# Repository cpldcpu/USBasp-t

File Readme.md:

## micro - USBasp ##

This is a work in progress. 

* Port of USBasp to ATtiny 85
* Design of optimized hardware

Why?

* It's fun.
* USBasp is a de-facto standard for small USB-AVR programmers. It's the only one to support TPI.
* Porting it to ATtiny85 allows for a smaller and cheaper circuit. Cheaper MCU, no Xtal, etc...

This software is based on Thomas Fischl's USBasp. See readme.txt for original comments.

### Status ####

Software:

* USBasp sucessfully compiles for the ATTiny85.
* micronucleus works as a bootloader.
* USB device is recognized as USBasp and communicates with AVRdude.
* Software tested on microUSB hardware. Both TPI and SPI seem to work.

Hardware:

* Revision 0.5 sent to OSH park for pcb manufacturing.
* Update v1.1 done, ready for manufacturing.
* Update 02/08/2013: All parts received, first device built.

### Flashing

* Flash micronucleus
* Set the fuses as in thuis Makefile: HFUSE=0x5d, LFUSE=0xe1, EFUSE=0xfe
* Flash the firmware with micronucleus

### Hardware ###

Circuit:  

v1.1 PCB front side:  

v1.1 PCB rear side:

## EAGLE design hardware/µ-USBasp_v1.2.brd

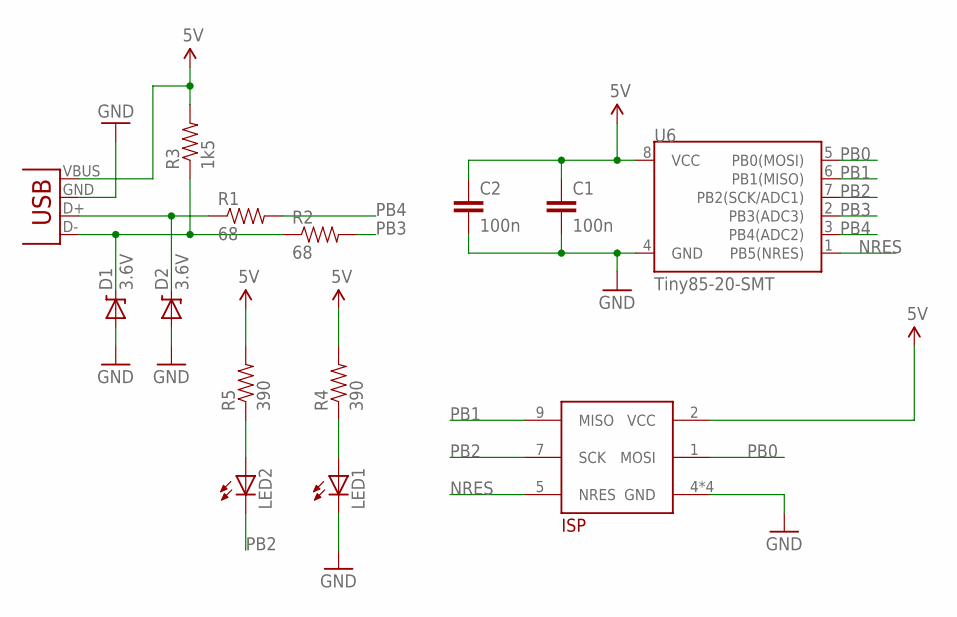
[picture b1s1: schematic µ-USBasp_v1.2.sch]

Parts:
C1, C2: 100n; 0805
D1, D2: 3.6V; SOD-323
JP2: USB-A-H
LED1, LED2: LEDCHIPLED_0805; CHIPLED_0805
R1, R2: 68; 0805
R3: 1k5; 0805
R4, R5: 390; 0805
U6: Tiny85-20-SMT; SO08-EIAJ
U$1: TB_ISPEDGE_2X5_LONG; ISP_EDGE2X5_LONG

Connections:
5V: C1.1, C2.1, JP2.VBUS (GND), R3.2, R4.2, R5.2, U6.8 (VCC), U$1.2 (VCC)
GND: C1.2, C2.2, D1.2 (A), D2.2 (A), JP2.GND (VBUS), LED1.C, U6.4 (GND), U$1.4 (GND), U$1.6 (GND), U$1.8 (GND), U$1.10 (GND)
unnamed: D1.1 (C), JP2.D- (D+), R2.1, R3.1
unnamed: D2.1 (C), JP2.D+ (D-), R1.1
unnamed: LED1.A, R4.1
unnamed: LED2.A, R5.1
NRES: U6.1 (PB5(NRES)), U$1.5 (NRES)
PB0: U6.5 (PB0(MOSI)), U$1.1 (MOSI)
PB1: U6.6 (PB1(MISO)), U$1.9 (MISO)
PB2: LED2.C, U6.7 (PB2(SCK/ADC1)), U$1.7 (SCK)
PB3: R2.2, U6.2 (PB3(ADC3))
PB4: R1.2, U6.3 (PB4(ADC2))

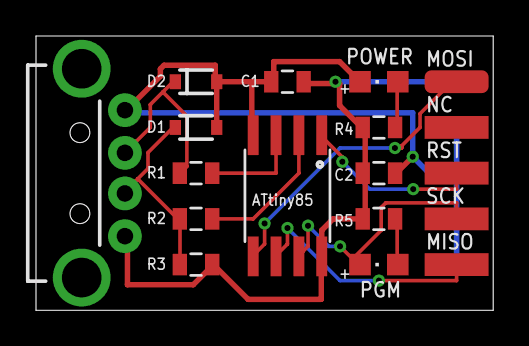
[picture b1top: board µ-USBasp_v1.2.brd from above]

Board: 2 copper layers, 25.4 x 15.2 mm, 15 parts (1 on the bottom side), 12 nets.

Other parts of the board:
U$2: OSHW-LOGO-M

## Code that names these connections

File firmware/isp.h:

/*
 * isp.h - part of USBasp
 *
 * Autor..........: Thomas Fischl <tfischl@gmx.de>
 * Description....: Provides functions for communication/programming
 *                  over ISP interface
 * Licence........: GNU GPL v2 (see Readme.txt)
 * Creation Date..: 2005-02-23
 * Last change....: 2009-02-28
 */

#ifndef __isp_h_included__
#define	__isp_h_included__

#ifndef uchar
#define	uchar	unsigned char
#endif

#ifdef __AVR_ATtiny85__

	#define	ISP_OUT   PORTB
	#define ISP_IN    PINB
	#define ISP_DDR   DDRB
	#define ISP_RST   PB5		
	#define ISP_MOSI  PB0		
	#define ISP_MISO  PB1		
	#define ISP_SCK   PB2		
	
#else

	#define	ISP_OUT   PORTB
	#define ISP_IN    PINB
	#define ISP_DDR   DDRB
	#define ISP_RST   PB2
	#define ISP_MOSI  PB3
	#define ISP_MISO  PB4
	#define ISP_SCK   PB5

#endif

/* Prepare connection to target device */
void ispConnect();

/* Close connection to target device */
void ispDisconnect();

/* read an write a byte from isp using software (slow) */
uchar ispTransmit_sw(uchar send_byte);

/* read an write a byte from isp using hardware (fast) */
uchar ispTransmit_hw(uchar send_byte);

/* enter programming mode */
uchar ispEnterProgrammingMode();

/* read byte from eeprom at given address */
uchar ispReadEEPROM(unsigned int address);

/* write byte to flash at given address */
uchar ispWriteFlash(unsigned long address, uchar data, uchar pollmode);

uchar ispFlushPage(unsigned long address, uchar pollvalue);

/* read byte from flash at given address */
uchar ispReadFlash(unsigned long address);

/* write byte to eeprom at given address */
uchar ispWriteEEPROM(unsigned int address, uchar data);

/* pointer to sw or hw transmit function */
uchar (*ispTransmit)(uchar);

/* set SCK speed. call before ispConnect! */
void ispSetSCKOption(uchar sckoption);

/* load extended address byte */
void ispLoadExtendedAddressByte(unsigned long address);

#endif /* __isp_h_included__ */

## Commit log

2013-06-28 Initial committ - 2011-05-28 w. new usbdrv
2013-06-28 First version of USBasp-t85 for ATtiny85
    USB Works, actual programming yet untested.
    No hardware SPI Support
    No LEDs
2013-06-29 PCB design
2013-06-29 makefile
2013-06-29 readme
2013-06-29 firmware snaptshop added
2013-06-29 Board v1.2
2013-06-29 v1.2
2013-08-02 hardware done
2022-05-23 update fuses and add gitignore
2022-05-23 add the extended fuses to the makefile

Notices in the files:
parts and their libraries:
SparkFun-Connectors: Licensing: CC v3.0 Share-Alike You are welcome to use this library for commercial purposes.
